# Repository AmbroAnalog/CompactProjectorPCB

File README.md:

# DIY CompactProjector Project

A compact 64x32 LCD monocrom projector build on the Project [diy-projector-clock](https://github.com/shufps/diy-projector-clock).
Perfectly suited for installation in narrow spaces with board dimensions of 38x86mm.

The LCD as well as the LED are controlled by an Arduino Pro Mini. The data for the Arduino can be sent via serial connection.

## List of components

  * 64x32 I2C LCD Screen ([allegro.pl](https://allegro.pl/oferta/art-lcd-vatn-64x32-3v-st7567a-i2c-15x12x2mm-whiten-6754828746))
  * 25mm C Mount Lens ([ebay.com](https://www.ebay.com/itm/255067829058?hash=item3b633a3342:g:b3sAAOSwA~9hBQYL))
  * Arduino Pro Mini 3,3V ([aliexpress.com](https://de.aliexpress.com/item/32821902128.html?spm=a2g0s.9042311.0.0.4a384c4dcQsU7K))
  * LED Lens ([aliexpress.com](https://de.aliexpress.com/item/1322969782.html?spm=a2g0s.9042311.0.0.4a384c4dcQsU7K))
  * BOM for PCB available in subfolder

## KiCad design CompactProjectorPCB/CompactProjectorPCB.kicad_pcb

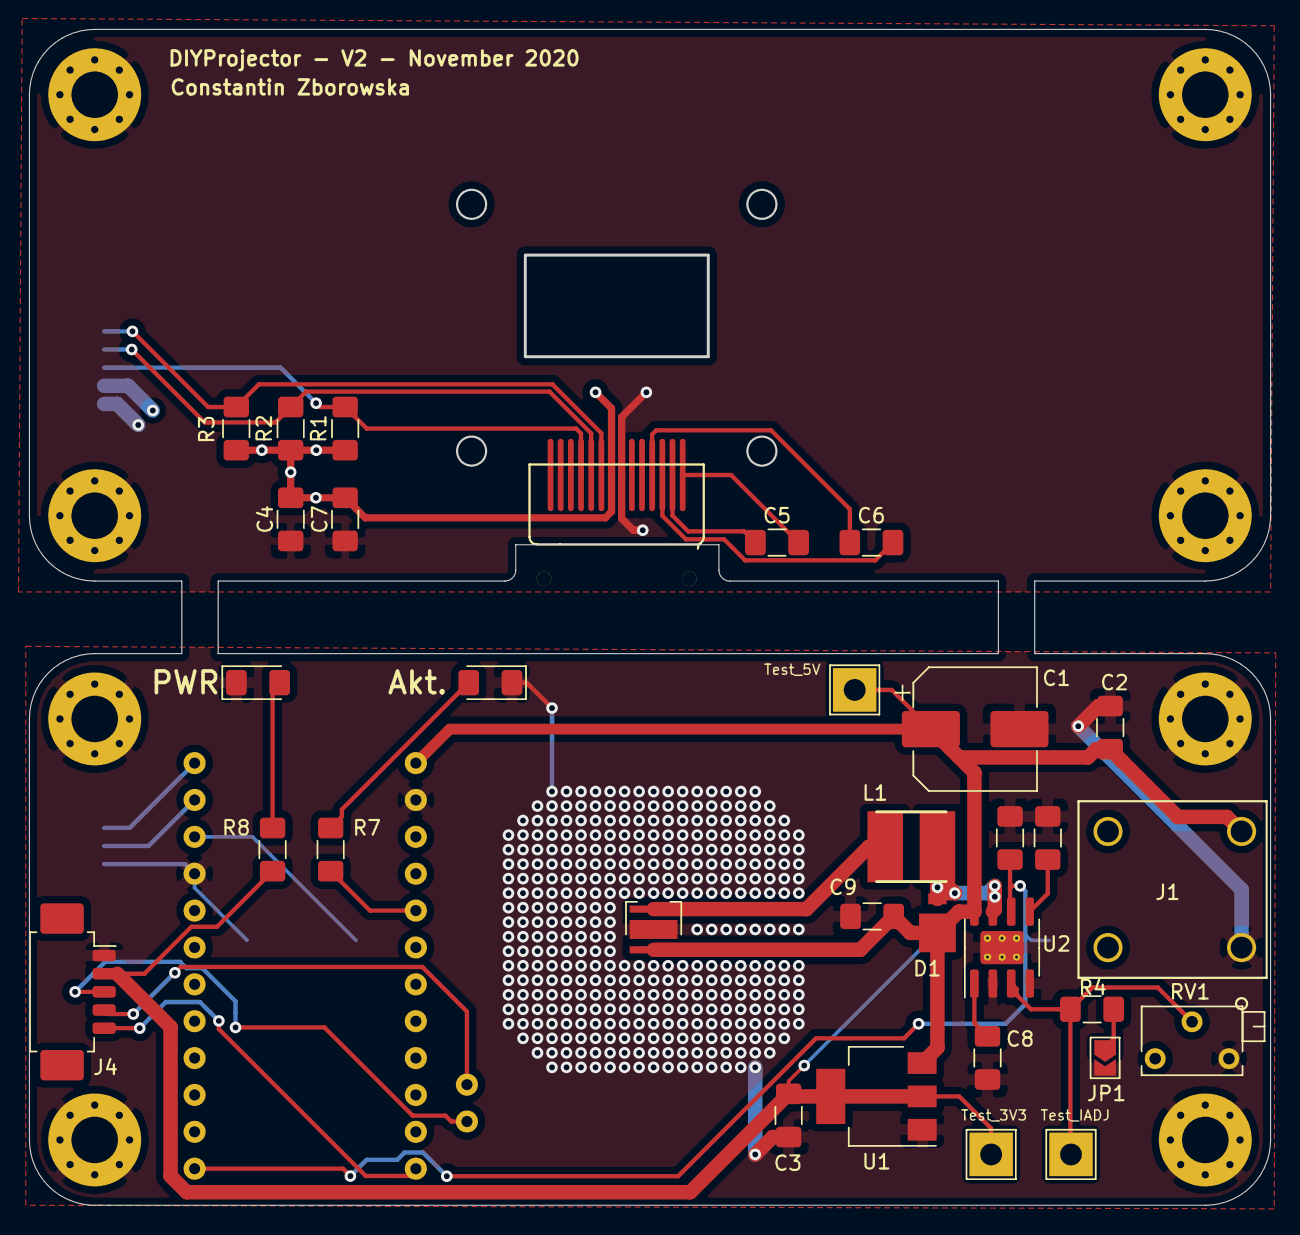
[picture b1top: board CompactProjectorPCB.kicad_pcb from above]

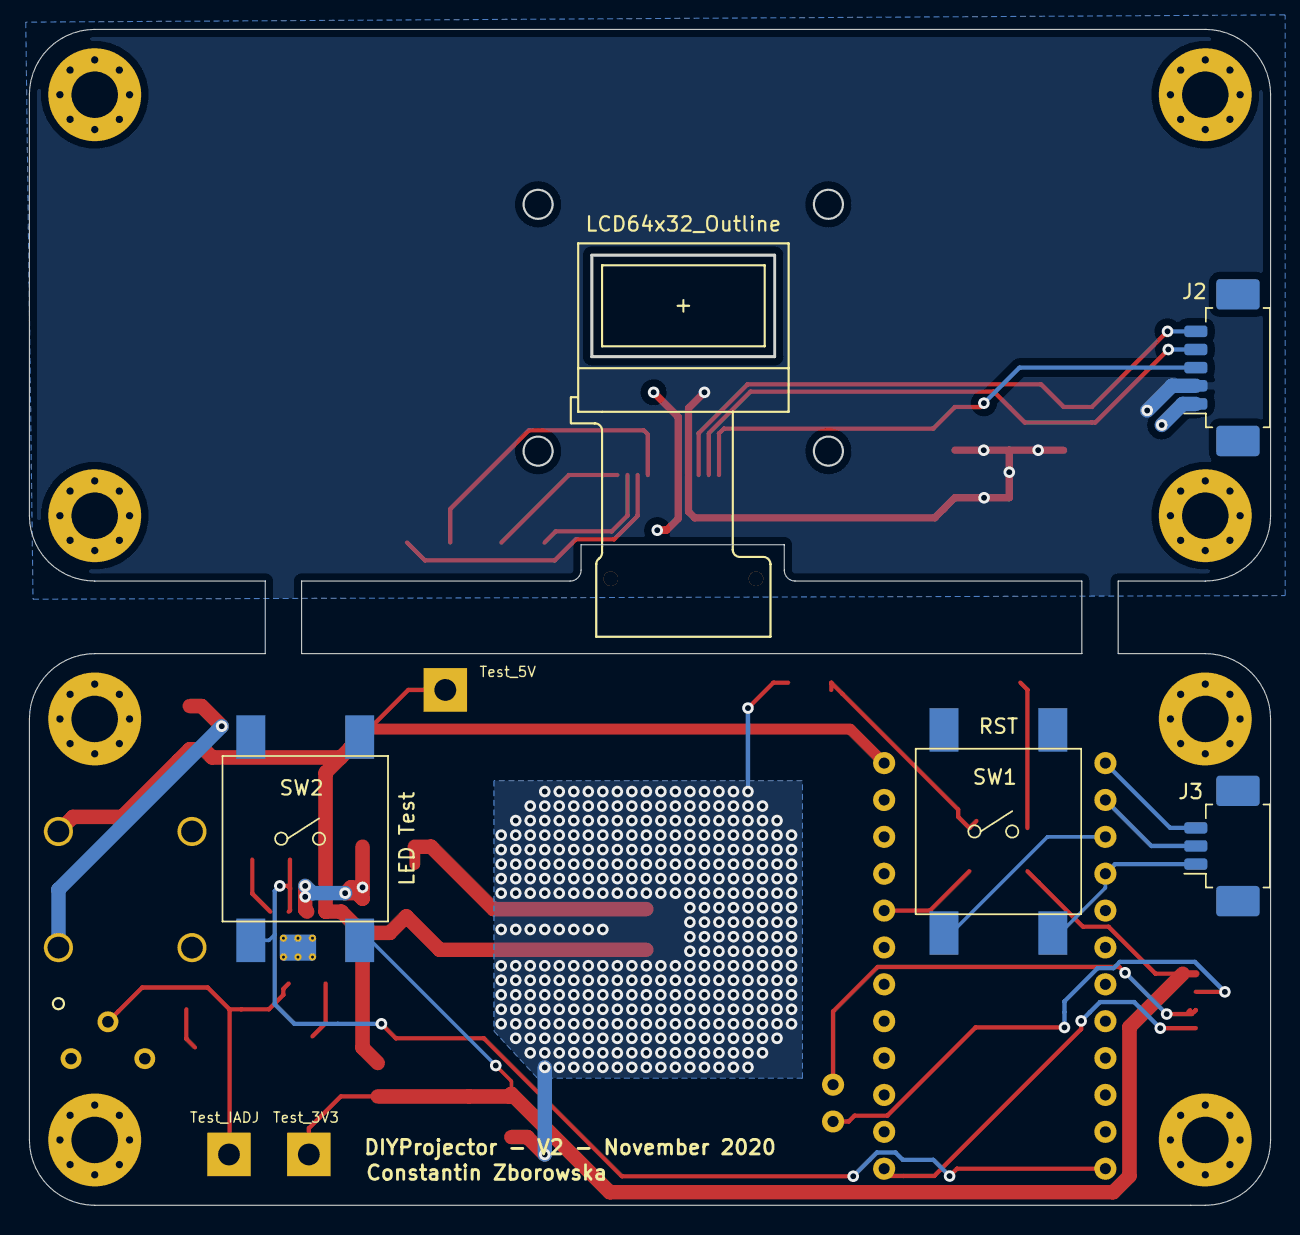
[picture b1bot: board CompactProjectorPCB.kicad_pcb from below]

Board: 2 copper layers, 85.4 x 80.9 mm, 45 parts (4 on the bottom side), 26 nets.

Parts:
C1: 150u; CP_Elec_8x6.7
C2, C3: 10u; C_1206_3216Metric_Pad1.42x1.75mm_HandSolder
C4: 100n; C_1206_3216Metric_Pad1.42x1.75mm_HandSolder
C5, C6, C7, C8: 1u; C_1206_3216Metric_Pad1.42x1.75mm_HandSolder
C9: 2,2u; C_1206_3216Metric_Pad1.42x1.75mm_HandSolder
D1: Schottky; DO-220AA
D2: CREE_XPE; LED_Cree-XP
D3: Gelb; LED_1206_3216Metric_Pad1.42x1.75mm_HandSolder
D4: Grün; LED_1206_3216Metric_Pad1.42x1.75mm_HandSolder
H1, H2, H3, H4, H5, H6, H7, H8: MountingHole_Pad; MountingHole_3.2mm_M3_Pad_Via
IC1: ArduinoProMini; Arduino_ProMini
J1: Screw_Terminal_01x02; Wago_2060-1872_1x02
J2, J4: Conn_01x05; Molex_PicoBlade_53261-0571_1x05-1MP_P1.25mm_Horizontal
J3: Conn_01x03; Molex_PicoBlade_53261-0371_1x03-1MP_P1.25mm_Horizontal
JP1: Jumper_NO; SolderJumper-2_P1.3mm_Open_TrianglePad1.0x1.5mm
L1: 10uH/1A; Wurth_WE-TPC_744043100
R1, R2: 2k2; R_1206_3216Metric_Pad1.42x1.75mm_HandSolder
R3, R6: 10k; R_1206_3216Metric_Pad1.42x1.75mm_HandSolder
R4: 4k7; R_1206_3216Metric_Pad1.42x1.75mm_HandSolder
R5: 20k; R_1206_3216Metric_Pad1.42x1.75mm_HandSolder
R7, R8: 68; R_1206_3216Metric_Pad1.42x1.75mm_HandSolder
RV1: R_POT; Potentiometer_Bourns_3266X_Horizontal
SW1: RST Button; Schurter_1241.1600
SW2: LED_Test Button; Schurter_1241.1600
TP1: TestPointIADJ; TestPoint_THTPad_3.0x3.0mm_Drill1.5mm
TP2: TestPoint3V3; TestPoint_THTPad_3.0x3.0mm_Drill1.5mm
TP3: TestPoint5V; TestPoint_THTPad_3.0x3.0mm_Drill1.5mm
U1: LD1117S33TR_SOT223; SOT-223-3_TabPin2
U2: LM3414; SOIC-8-1EP_3.9x4.9mm_P1.27mm_EP2.29x3mm_ThermalVias
U3: LCD64x32

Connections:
+3V3: C3.1, C4.1, C7.1, J2.2, J4.2, R1.1, R2.1, R3.1, R8.2, SW2.2, TP2.1, U1.2, U3.8
+5V: C1.1, C2.1, C9.2, D1.1, D2.2, IC1.34, J1.2, TP3.1, U1.3, U2.8
GND: C1.2, C2.2, C3.2, C4.2, C7.2, C8.1, C9.1, D2.3, D3.1, D4.1, H1.1, H2.1, H3.1, H4.1, H5.1, H6.1, H7.1, H8.1, IC1.30, IC1.31, J1.1, J2.1, J3.1, J4.1, JP1.2, R5.2, R6.2, RV1.3, SW1.2, U1.1, U2.2, U2.4, U2.9, U3.7
LED_PWM: IC1.9, R6.1, SW2.1, U2.6
unnamed: C5.1, U3.2
unnamed: C5.2, U3.1
unnamed: C6.1, U3.3
unnamed: C6.2, U3.4
unnamed: C8.2, U2.1
unnamed: D1.2, L1.1, U2.7
unnamed: D2.1, L1.2
unnamed: D3.2, R7.1
unnamed: D4.2, R8.1
unnamed: IC1.0, J3.2
unnamed: IC1.1, J3.3
unnamed: IC1.10, J4.5
unnamed: IC1.17, R7.2
unnamed: IC1.18, J4.3
unnamed: IC1.19, J4.4
unnamed: IC1.33, SW1.1
unnamed: J2.3, R1.2, U3.11
unnamed: J2.4, R2.2, U3.10
unnamed: J2.5, R3.2, U3.9
unnamed: JP1.1, R4.2
unnamed: R4.1, RV1.2, TP1.1, U2.3
unnamed: R5.1, U2.5

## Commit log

2021-09-02 add program state modes
2021-09-08 change bus clock speed for stabiliti

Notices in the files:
parts and their libraries:
Copyright 2016 Accelerated Designs. All rights reserved.
